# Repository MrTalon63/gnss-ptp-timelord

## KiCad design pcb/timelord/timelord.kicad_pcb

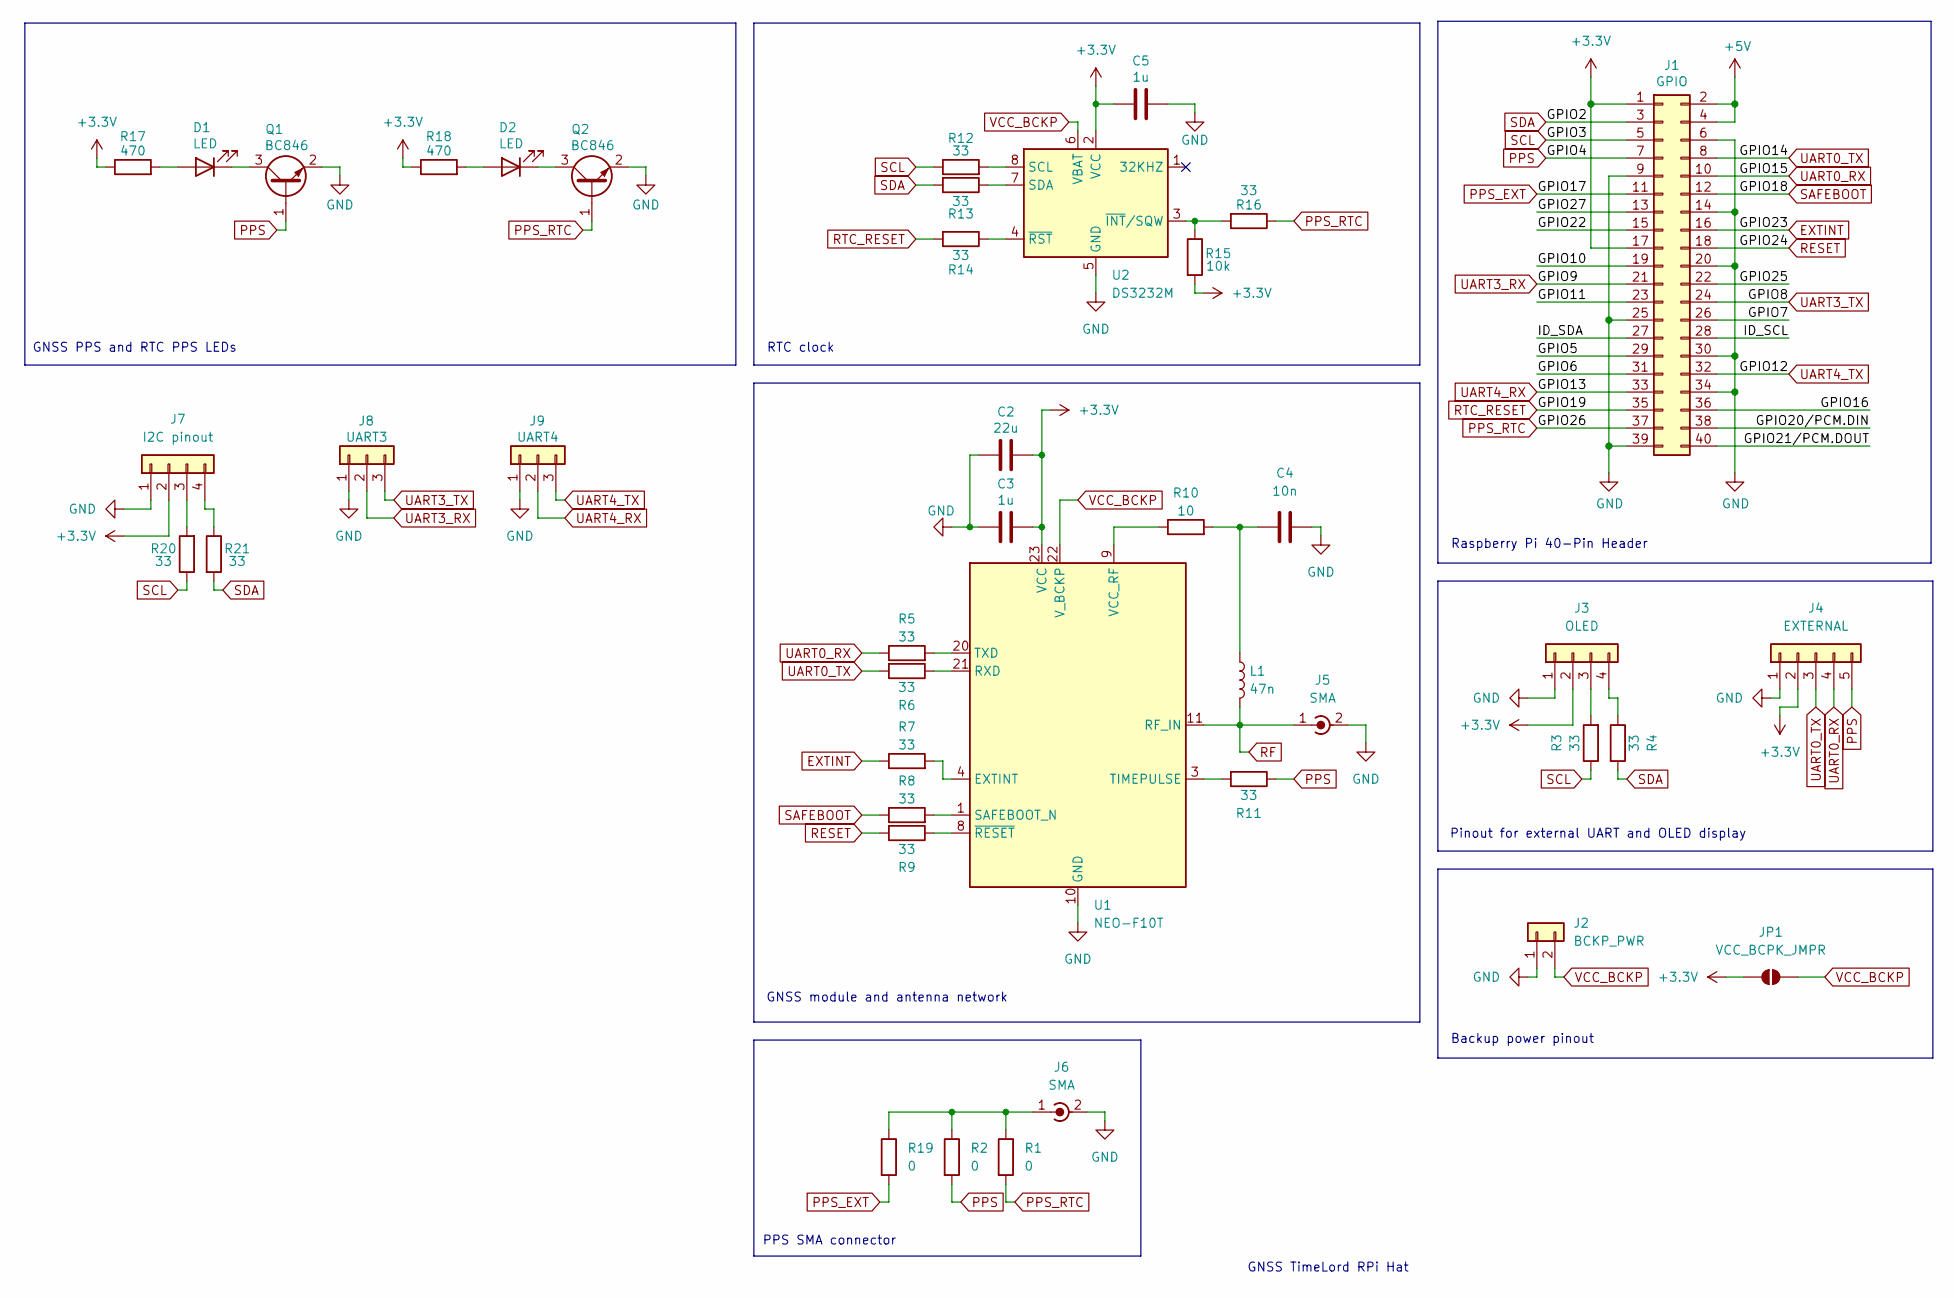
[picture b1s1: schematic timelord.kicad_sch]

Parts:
C2: 22u; C_0805_2012Metric
C3, C5: 1u; C_0603_1608Metric
C4: 10n; C_0805_2012Metric
D1, D2: LED; LED_0603_1608Metric
J1: GPIO; PinSocket_2x20_P2.54mm_Vertical
J2: BCKP_PWR; PinHeader_1x02_P2.54mm_Vertical
J3: OLED; PinSocket_1x04_P2.54mm_Vertical
J4: EXTERNAL; PinHeader_1x05_P2.54mm_Vertical
J5, J6: SMA; SMA_Amphenol_132289_EdgeMount
J7: I2C pinout; PinSocket_1x04_P2.54mm_Vertical
J8: UART3; PinHeader_1x03_P2.54mm_Vertical
J9: UART4; PinHeader_1x03_P2.54mm_Vertical
JP1: VCC_BCPK_JMPR; SolderJumper-2_P1.3mm_Open_TrianglePad1.0x1.5mm
L1: 47n; L_0603_1608Metric
Q1, Q2: BC846; SOT-23
R1, R2, R19: 0; R_0603_1608Metric
R3, R4, R5, R6, R7, R8, R9, R11, R12, R13, R14, R16, R20, R21: 33; R_0603_1608Metric
R10: 10; R_0805_2012Metric
R15: 10k; R_0805_2012Metric
R17, R18: 470; R_0603_1608Metric
U1: NEO-F10T; ublox_NEO
U2: DS3232M; SOIC-8_3.9x4.9mm_P1.27mm

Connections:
+3.3V: C2.2, C3.2, C5.1, J1.1, J1.17, J3.2, J4.2, J7.2, JP1.1 (A), R15.2, R17.1, R18.1, U1.23 (VCC), U2.2 (VCC)
+5V: J1.2, J1.4
/GPIO5: J1.29
/GPIO6: J1.31
/GPIO7: J1.26
/GPIO10: J1.19
/GPIO11: J1.23
/GPIO16: J1.36
/GPIO20/PCM.DIN: J1.38
/GPIO21/PCM.DOUT: J1.40
/GPIO22: J1.15
/GPIO25: J1.22
/GPIO27: J1.13
/ID_SCL: J1.28
/ID_SDA: J1.27
EXTINT: J1.16, R7.1
GND: C2.1, C3.1, C4.2, C5.2, J1.6, J1.9, J1.14, J1.20, J1.25, J1.30, J1.34, J1.39, J2.1, J3.1, J4.1, J5.2 (Ext), J6.2 (Ext), J7.1, J8.1, J9.1, Q1.2 (E), Q2.2 (E), U1.10 (GND), U1.12 (GND), U1.13 (GND), U1.24 (GND), U2.5 (GND)
unnamed: C4.1, L1.1, R10.2
unnamed: D1.2 (A), R17.2
unnamed: D1.1 (K), Q1.3 (C)
unnamed: D2.2 (A), R18.2
unnamed: D2.1 (K), Q2.3 (C)
unnamed: J3.3, R3.2
unnamed: J3.4, R4.1
unnamed: J6.1 (In), R1.1, R2.1, R19.1
unnamed: J7.3, R20.2
unnamed: J7.4, R21.1
unnamed: R7.2, U1.4 (EXTINT)
unnamed: R6.1, U1.21 (RXD)
unnamed: R8.2, U1.1 (SAFEBOOT_N)
unnamed: R11.2, U1.3 (TIMEPULSE)
unnamed: R5.2, U1.20 (TXD)
unnamed: R10.1, U1.9 (VCC_RF)
unnamed: R9.1, U1.8 (~RESET)
unnamed: R12.2, U2.8 (SCL)
unnamed: R13.1, U2.7 (SDA)
unnamed: R15.1, R16.2, U2.3 (~INT/SQW)
unnamed: R14.1, U2.4 (~RST)
PPS: J1.7, J4.5, Q1.1 (B), R2.2, R11.1
PPS_EXT: J1.11, R19.2
PPS_RTC: J1.37, Q2.1 (B), R1.2, R16.1
RESET: J1.18, R9.2
RF: J5.1 (In), L1.2, U1.11 (RF_IN)
RTC_RESET: J1.35, R14.2
SAFEBOOT: J1.12, R8.1
SCL: J1.5, R3.1, R12.1, R20.1
SDA: J1.3, R4.2, R13.2, R21.2
UART0_RX: J1.10, J4.4, R5.1
UART0_TX: J1.8, J4.3, R6.2
UART3_RX: J1.21, J8.2
UART3_TX: J1.24, J8.3
UART4_RX: J1.33, J9.2
UART4_TX: J1.32, J9.3
VCC_BCKP: J2.2, JP1.2 (B), U1.22 (V_BCKP), U2.6 (VBAT)

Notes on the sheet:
RTC clock
GNSS PPS and RTC PPS LEDs
PPS SMA connector
Backup power pinout
GNSS TimeLord RPi Hat
Pinout for external UART and OLED display
GNSS module and antenna network
Raspberry Pi 40-Pin Header

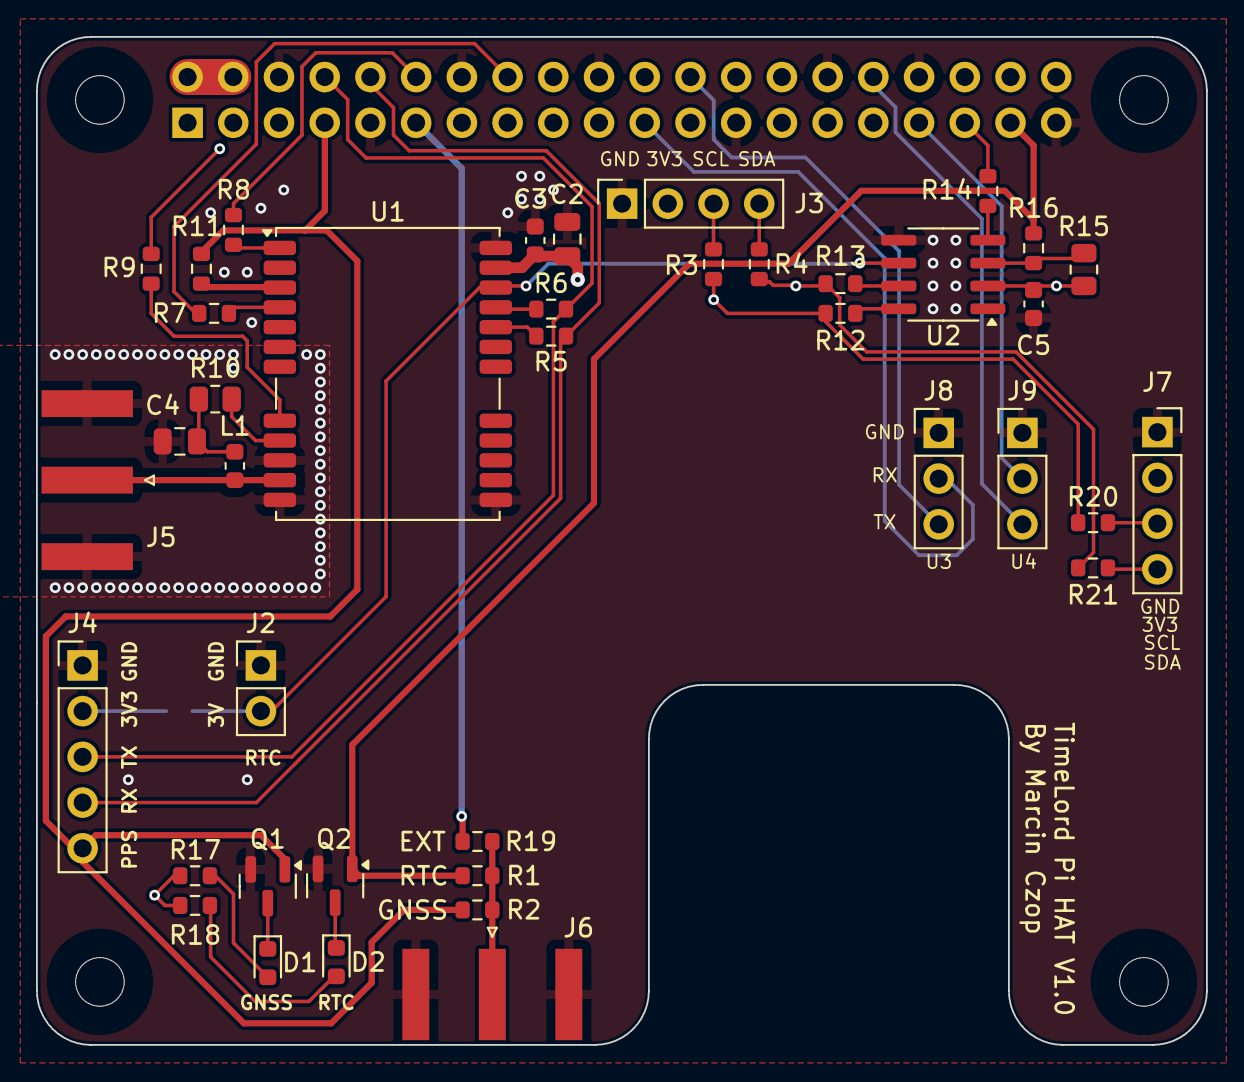
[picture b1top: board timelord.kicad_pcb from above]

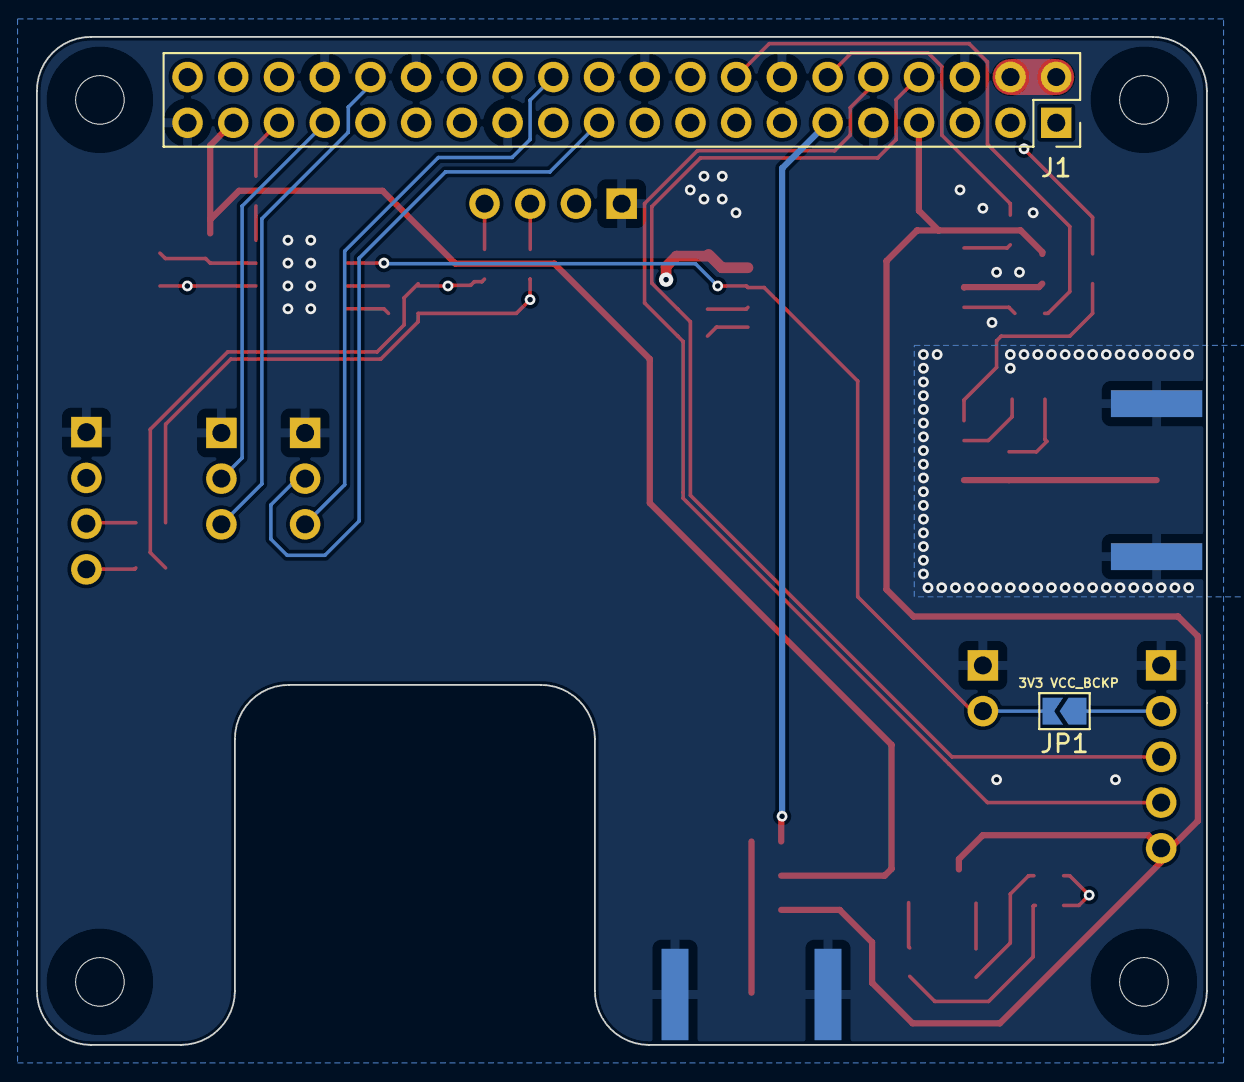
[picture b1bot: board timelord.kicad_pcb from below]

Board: 4 copper layers, 65.0 x 56.0 mm, 46 parts (2 on the bottom side), 41 nets.

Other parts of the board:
MH1, MH2, MH3, MH4: MountingHole_2.7mm_M2.5

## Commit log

2025-03-16 Preview schematic and PCB design files
2025-03-16 Add external I2C RTC
2025-03-16 Redesign board edges and add backup power
2025-03-16 Cosmetic changes
2025-03-19 Make rounded corners more rounded
2025-03-20 Rearrange components
2025-03-21 Fix MFRs and component sizing
2025-03-22 Reworked RF part of the PCB
2025-03-24 Add SMA PPS connector and change 5V plane to GND plane
